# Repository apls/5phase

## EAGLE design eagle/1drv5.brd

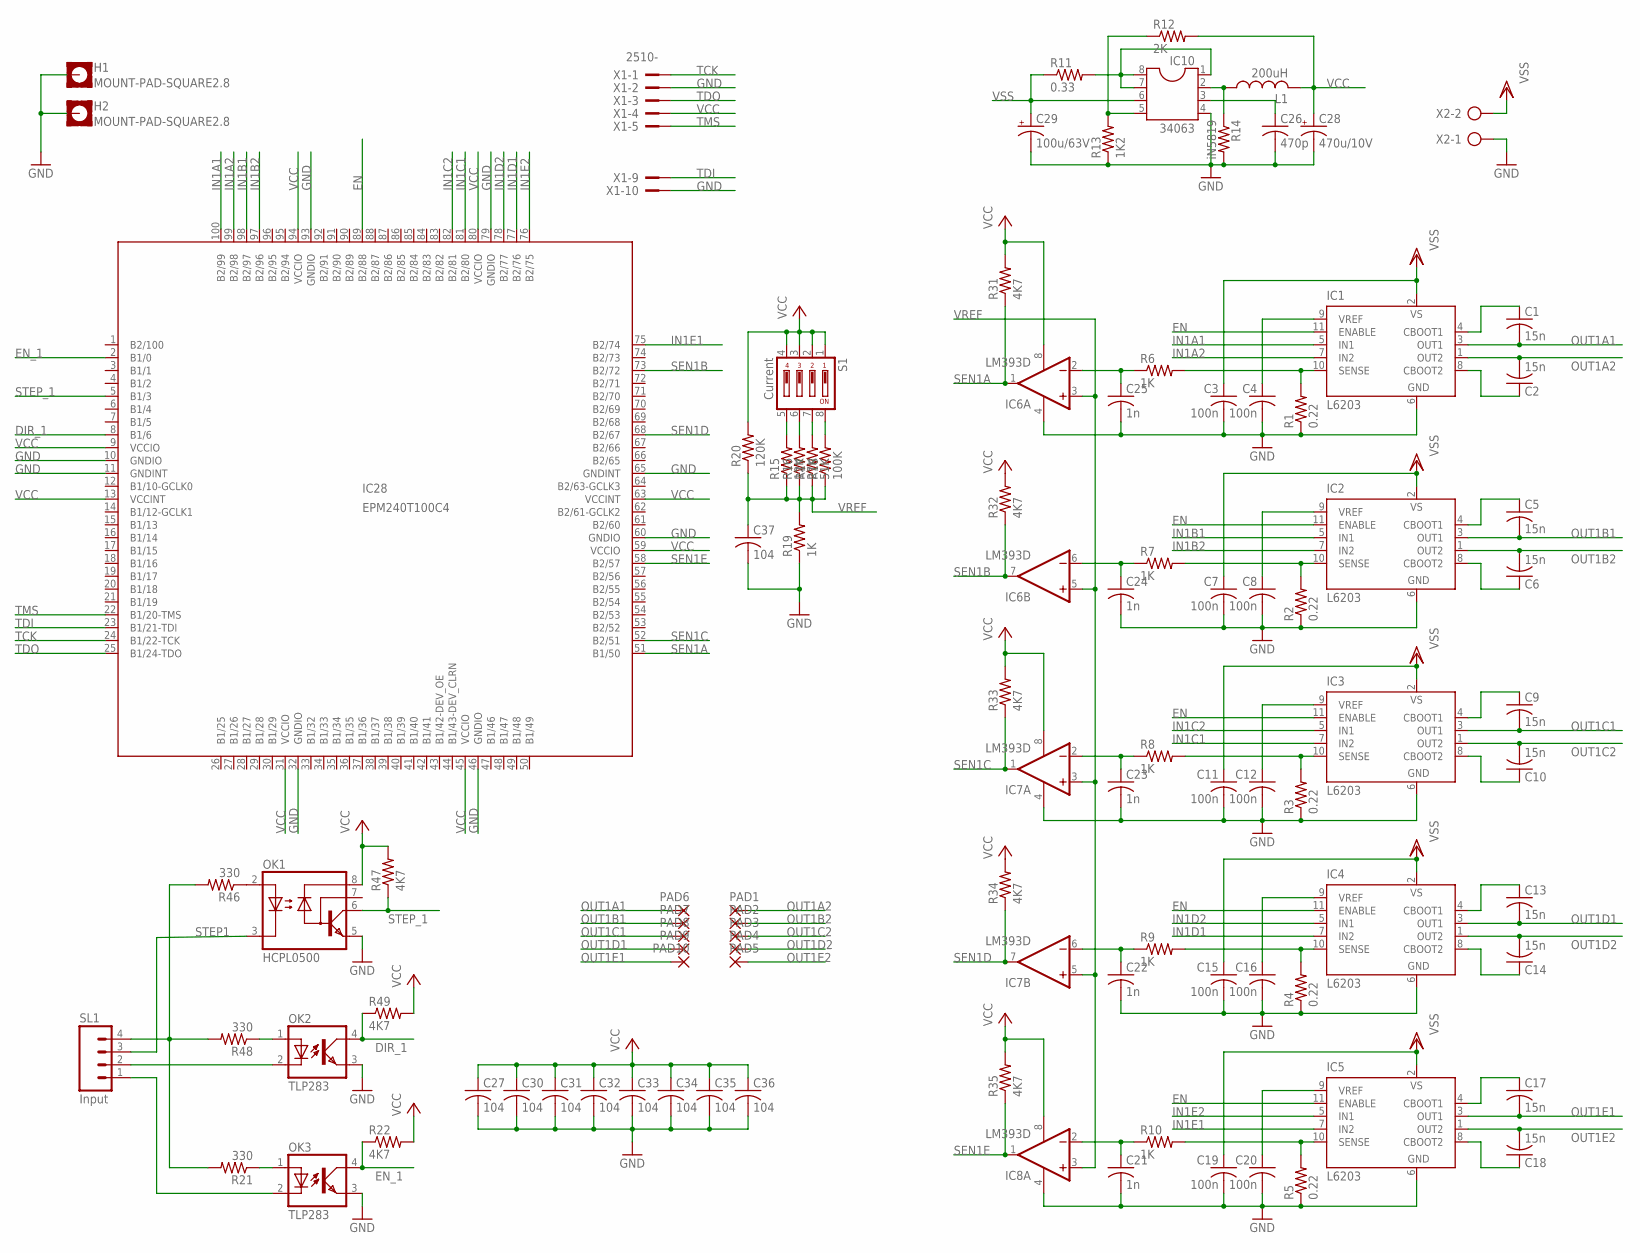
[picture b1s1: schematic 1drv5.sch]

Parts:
C1, C2, C5, C6, C9, C10, C13, C14, C17, C18: 15n; C050-024X044
C3, C7, C11, C15, C19: 100n; C150-064X183
C4, C8, C12, C16, C20: 100n; C050-025X075
C21, C22, C23, C24, C25: 1n; C1206
C26: 470p; C1206
C27, C30, C31, C32, C33, C34, C35, C36, C37: 104; C1206
C28: 470u/10V; E3,5-8
C29: 100u/63V; E5-8,5
H1, H2: MOUNT-PAD-SQUARE2.8; 2,8-PAD-SQUARE
IC1, IC2, IC3, IC4, IC5: L6203; MULTIWATT-11
IC6, IC7, IC8: LM393D; SO08
IC10: 34063; DIL08
IC28: EPM240T100C4; TQFP100
L1: 200uH; 0207/5V
OK1: HCPL0500; SOIC08
OK2, OK3: TLP283; MINI-FLAT-4
PAD1, PAD2, PAD3, PAD4, PAD5, PAD6, PAD7, PAD8, PAD9, PAD10: 1,6/0,8
R1, R2, R3, R4, R5: 0.22; 0411V
R6, R7, R8, R9, R10, R19: 1K; R1206
R11: 0.33; 0207/7
R12: 2K; 0207/7
R13: 1K2; 0207/7
R14: iN5819; 0414V
R15: 12K; R1206
R16: 27K; R1206
R17: 51K; R1206
R18: 100K; R1206
R20: 120K; R1206
R21, R46, R48: 330; R1206
R22, R31, R32, R33, R34, R35, R47, R49: 4K7; R1206
S1: Current; DP-04
SL1: Input; 04P
X1: 2510-; PAK100/2500-10
X2: AK500/2-H

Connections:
DIR_1: IC28.8 (B1/6), OK2.4 (COL), R49.1
EN: IC1.11 (ENABLE), IC2.11 (ENABLE), IC3.11 (ENABLE), IC4.11 (ENABLE), IC5.11 (ENABLE), IC28.89 (B2/88)
EN_1: IC28.2 (B1/0), OK3.4 (COL), R22.1
GND: C3.2, C4.2, C7.2, C8.2, C11.2, C12.2, C15.2, C16.2, C19.2, C20.2, C21.2, C22.2, C23.2, C24.2, C25.2, C26.2, C27.2, C28.-, C29.-, C30.2, C31.2, C32.2, C33.2, C34.2, C35.2, C36.2, C37.2, H1.B2,8, H2.B2,8, IC1.6 (GND), IC2.6 (GND), IC3.6 (GND), IC4.6 (GND), IC5.6 (GND), IC6.4 (V-), IC7.4 (V-), IC8.4 (V-), IC10.4, IC28.10 (GNDIO), IC28.11 (GNDINT), IC28.32 (GNDIO), IC28.46 (GNDIO), IC28.60 (GNDIO), IC28.65 (GNDINT), IC28.79 (GNDIO), IC28.93 (GNDIO), OK1.5 (GND), OK2.3 (EMIT), OK3.3 (EMIT), R1.1, R2.1, R3.1, R4.1, R5.1, R13.1, R14.2, R19.1, X1.2, X1.10, X2.1
IN1A1: IC1.5 (IN1), IC28.100 (B2/99)
IN1A2: IC1.7 (IN2), IC28.99 (B2/98)
IN1B1: IC2.5 (IN1), IC28.98 (B2/97)
IN1B2: IC2.7 (IN2), IC28.97 (B2/96)
IN1C1: IC3.7 (IN2), IC28.81 (B2/80)
IN1C2: IC3.5 (IN1), IC28.82 (B2/81)
IN1D1: IC4.7 (IN2), IC28.77 (B2/76)
IN1D2: IC4.5 (IN1), IC28.78 (B2/77)
IN1E1: IC5.7 (IN2), IC28.75 (B2/74)
IN1E2: IC5.5 (IN1), IC28.76 (B2/75)
unnamed: C8.1, IC2.9 (VREF)
unnamed: C1.1, IC1.4 (CBOOT1)
unnamed: C2.1, IC1.8 (CBOOT2)
unnamed: C4.1, IC1.9 (VREF)
unnamed: C5.1, IC2.4 (CBOOT1)
unnamed: C6.1, IC2.8 (CBOOT2)
unnamed: C12.1, IC3.9 (VREF)
unnamed: C9.1, IC3.4 (CBOOT1)
unnamed: C10.1, IC3.8 (CBOOT2)
unnamed: C16.1, IC4.9 (VREF)
unnamed: C13.1, IC4.4 (CBOOT1)
unnamed: C14.1, IC4.8 (CBOOT2)
unnamed: C20.1, IC5.9 (VREF)
unnamed: C17.1, IC5.4 (CBOOT1)
unnamed: C18.1, IC5.8 (CBOOT2)
unnamed: C25.1, IC6.2 (-IN), R6.1
unnamed: C21.1, IC8.2 (-IN), R10.1
unnamed: IC10.2, L1.1, R14.1
unnamed: C22.1, IC7.6 (-IN), R9.1
unnamed: OK2.1 (A), R48.1
unnamed: C23.1, IC7.2 (-IN), R8.1
unnamed: C26.1, IC10.3
unnamed: C24.1, IC6.6 (-IN), R7.1
unnamed: OK2.2 (C), SL1.2
unnamed: IC10.1, IC10.7, IC10.8, R11.2
unnamed: R15.2, S1.5
unnamed: R16.2, S1.6
unnamed: IC10.5, R12.1, R13.2
unnamed: R17.2, S1.7
unnamed: R18.2, S1.8
unnamed: R21.2, R46.2, R48.2, SL1.4
unnamed: OK3.1 (A), R21.1
unnamed: OK3.2 (C), SL1.1
unnamed: OK1.2 (A), R46.1
OUT1A1: C1.2, IC1.3 (OUT1), PAD6.1
OUT1A2: C2.2, IC1.1 (OUT2), PAD1.1
OUT1B1: C5.2, IC2.3 (OUT1), PAD7.1
OUT1B2: C6.2, IC2.1 (OUT2), PAD2.1
OUT1C1: C9.2, IC3.3 (OUT1), PAD8.1
OUT1C2: C10.2, IC3.1 (OUT2), PAD3.1
OUT1D1: C13.2, IC4.3 (OUT1), PAD9.1
OUT1D2: C14.2, IC4.1 (OUT2), PAD4.1
OUT1E1: C17.2, IC5.3 (OUT1), PAD10.1
OUT1E2: C18.2, IC5.1 (OUT2), PAD5.1
SEN1A: IC6.1 (OUT), IC28.51 (B1/50), R31.1
SEN1B: IC6.7 (OUT), IC28.73 (B2/72), R32.1
SEN1C: IC7.1 (OUT), IC28.52 (B2/51), R33.1
SEN1D: IC7.7 (OUT), IC28.68 (B2/67), R34.1
SEN1E: IC8.1 (OUT), IC28.58 (B2/57), R35.1
SEN_A: IC1.10 (SENSE), R1.2, R6.2
SEN_B: IC2.10 (SENSE), R2.2, R7.2
SEN_C: IC3.10 (SENSE), R3.2, R8.2
SEN_D: IC4.10 (SENSE), R4.2, R9.2
SEN_E: IC5.10 (SENSE), R5.2, R10.2
STEP1: OK1.3 (C), SL1.3
STEP_1: IC28.5 (B1/3), OK1.6 (VO), R47.1
TCK: IC28.24 (B1/22-TCK), X1.1
TDI: IC28.23 (B1/21-TDI), X1.9
TDO: IC28.25 (B1/24-TDO), X1.3
TMS: IC28.22 (B1/20-TMS), X1.5
VCC: C27.1, C28.+, C30.1, C31.1, C32.1, C33.1, C34.1, C35.1, C36.1, IC6.8 (V+), IC7.8 (V+), IC8.8 (V+), IC28.9 (VCCIO), IC28.13 (VCCINT), IC28.31 (VCCIO), IC28.45 (VCCIO), IC28.59 (VCCIO), IC28.63 (VCCINT), IC28.80 (VCCIO), IC28.94 (VCCIO), L1.2, OK1.8 (VCC), R12.2, R20.2, R22.2, R31.2, R32.2, R33.2, R34.2, R35.2, R47.2, R49.2, S1.1, S1.2, S1.3, S1.4, X1.4
VREF: C37.1, IC6.3 (+IN), IC6.5 (+IN), IC7.3 (+IN), IC7.5 (+IN), IC8.3 (+IN), R15.1, R16.1, R17.1, R18.1, R19.2, R20.1
VSS: C3.1, C7.1, C11.1, C15.1, C19.1, C29.+, IC1.2 (VS), IC2.2 (VS), IC3.2 (VS), IC4.2 (VS), IC5.2 (VS), IC10.6, R11.1, X2.2

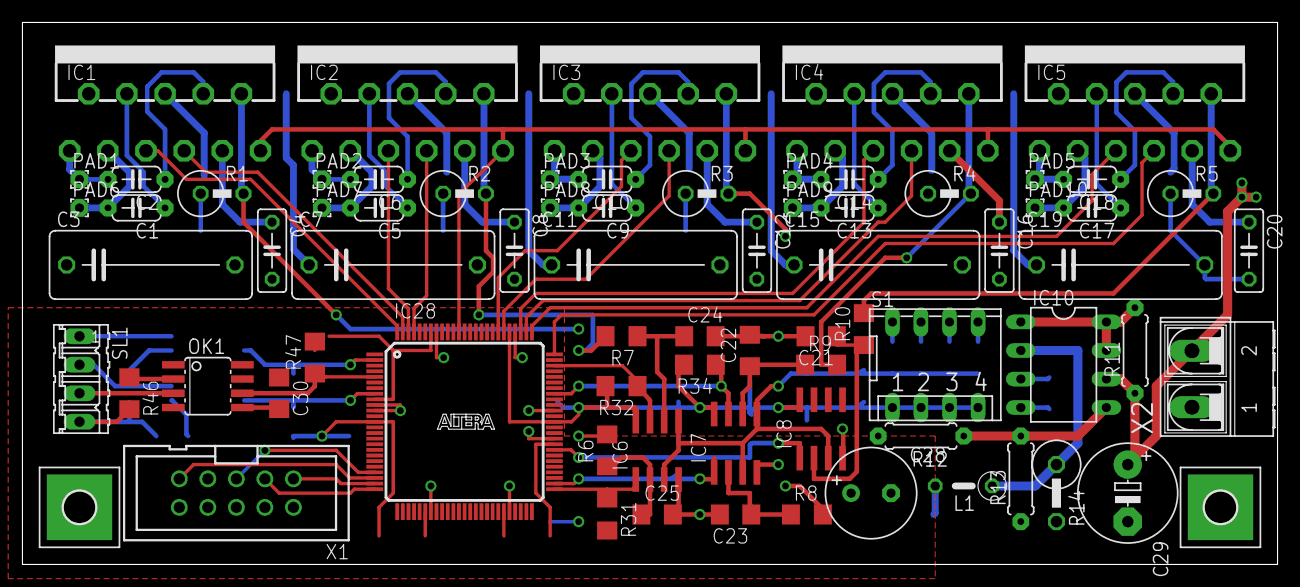
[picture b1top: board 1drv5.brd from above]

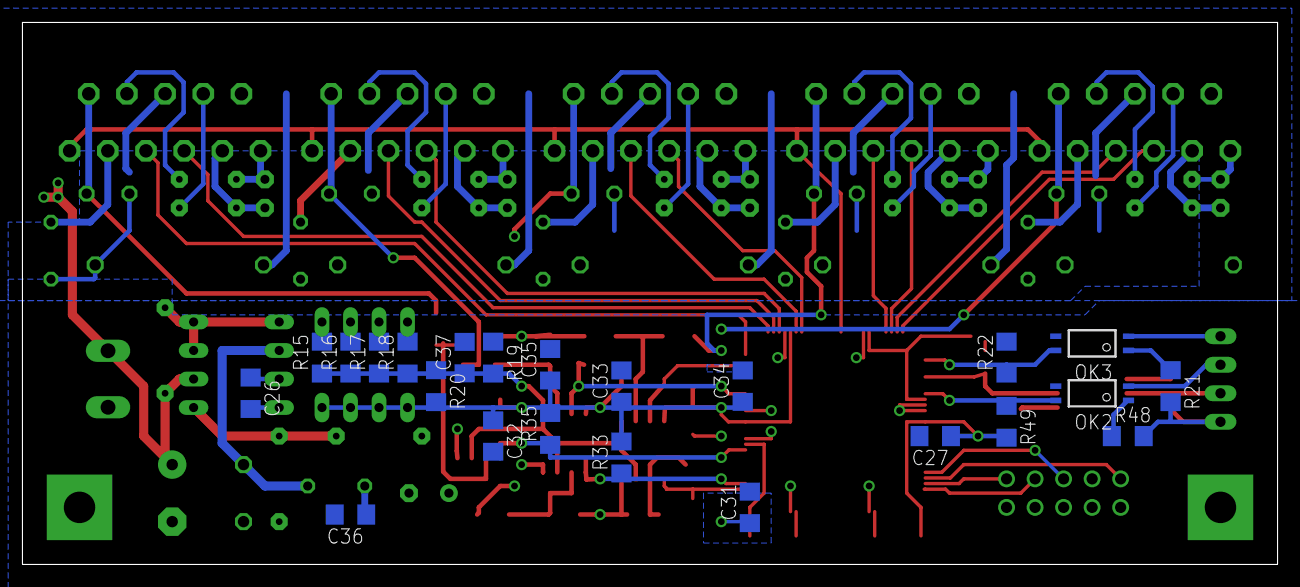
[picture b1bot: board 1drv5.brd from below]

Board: 2 copper layers, 111.8 x 48.3 mm, 98 parts (23 on the bottom side), 77 nets.

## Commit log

2015-12-12 create commit
2015-12-12 version 0.1 Signed-off-by: apls <bj300002@sina.com>
